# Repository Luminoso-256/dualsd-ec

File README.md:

# dualsd-ec
SD + MicroSD in one expansion card. It's a tight fit!

Based on the framework PCB template. Case is modified from the non-retrofit one, and doctored up to fit the slightly oversized PCB.

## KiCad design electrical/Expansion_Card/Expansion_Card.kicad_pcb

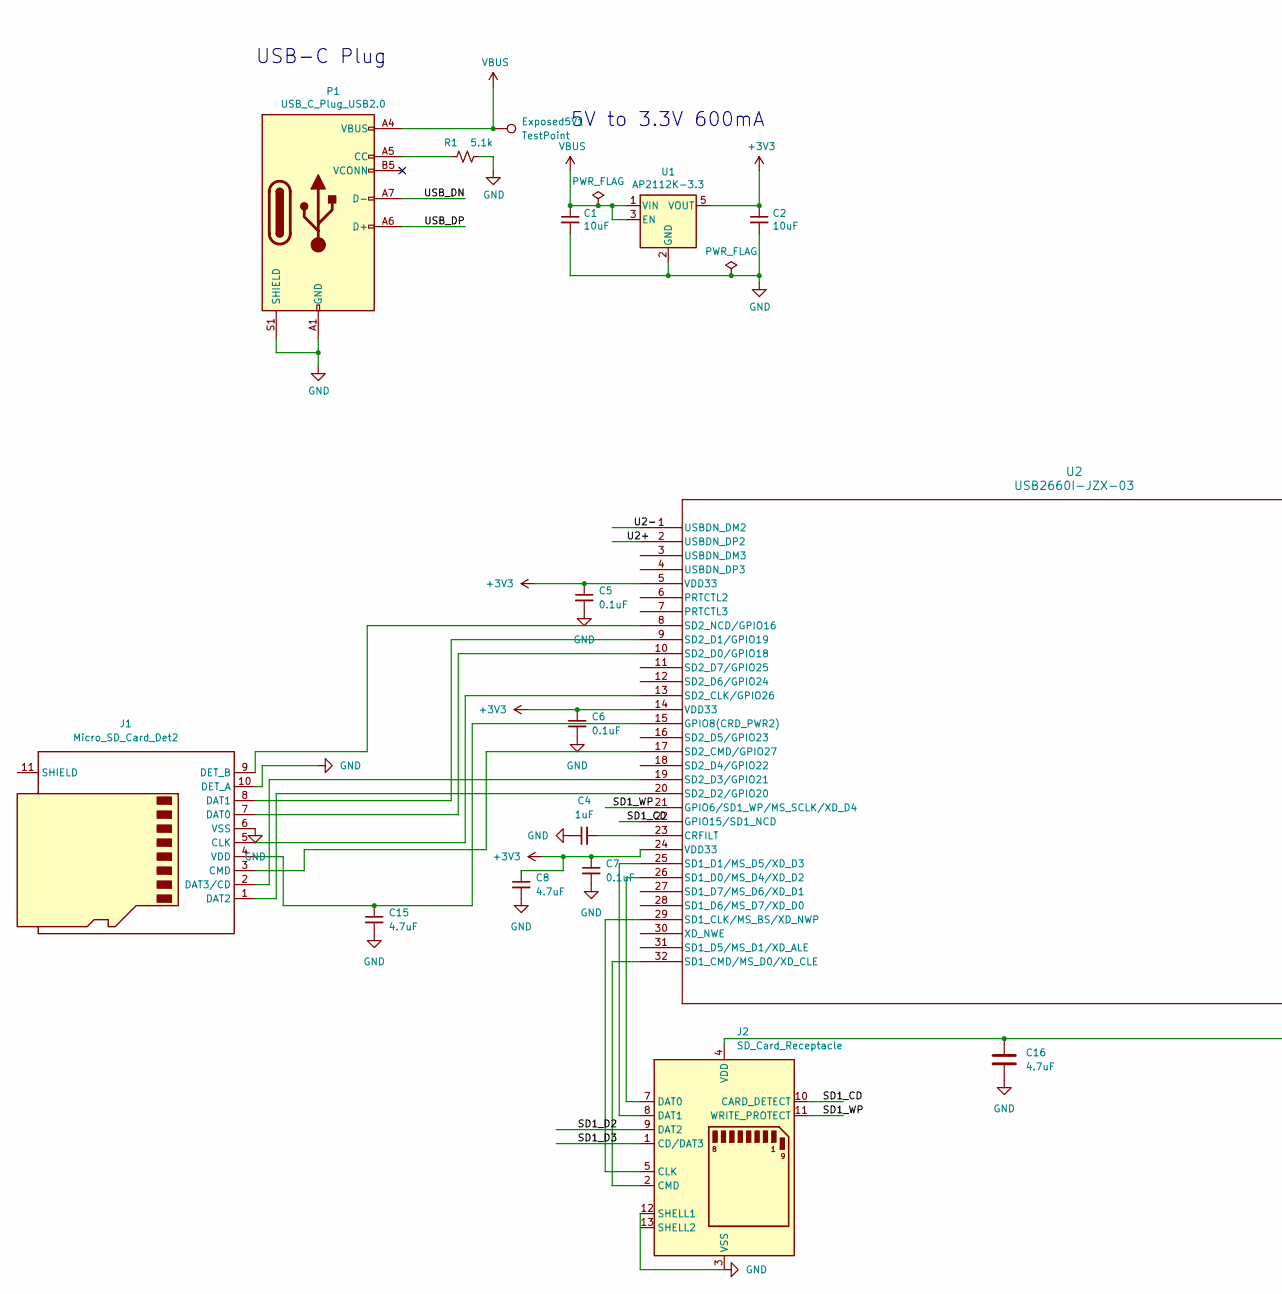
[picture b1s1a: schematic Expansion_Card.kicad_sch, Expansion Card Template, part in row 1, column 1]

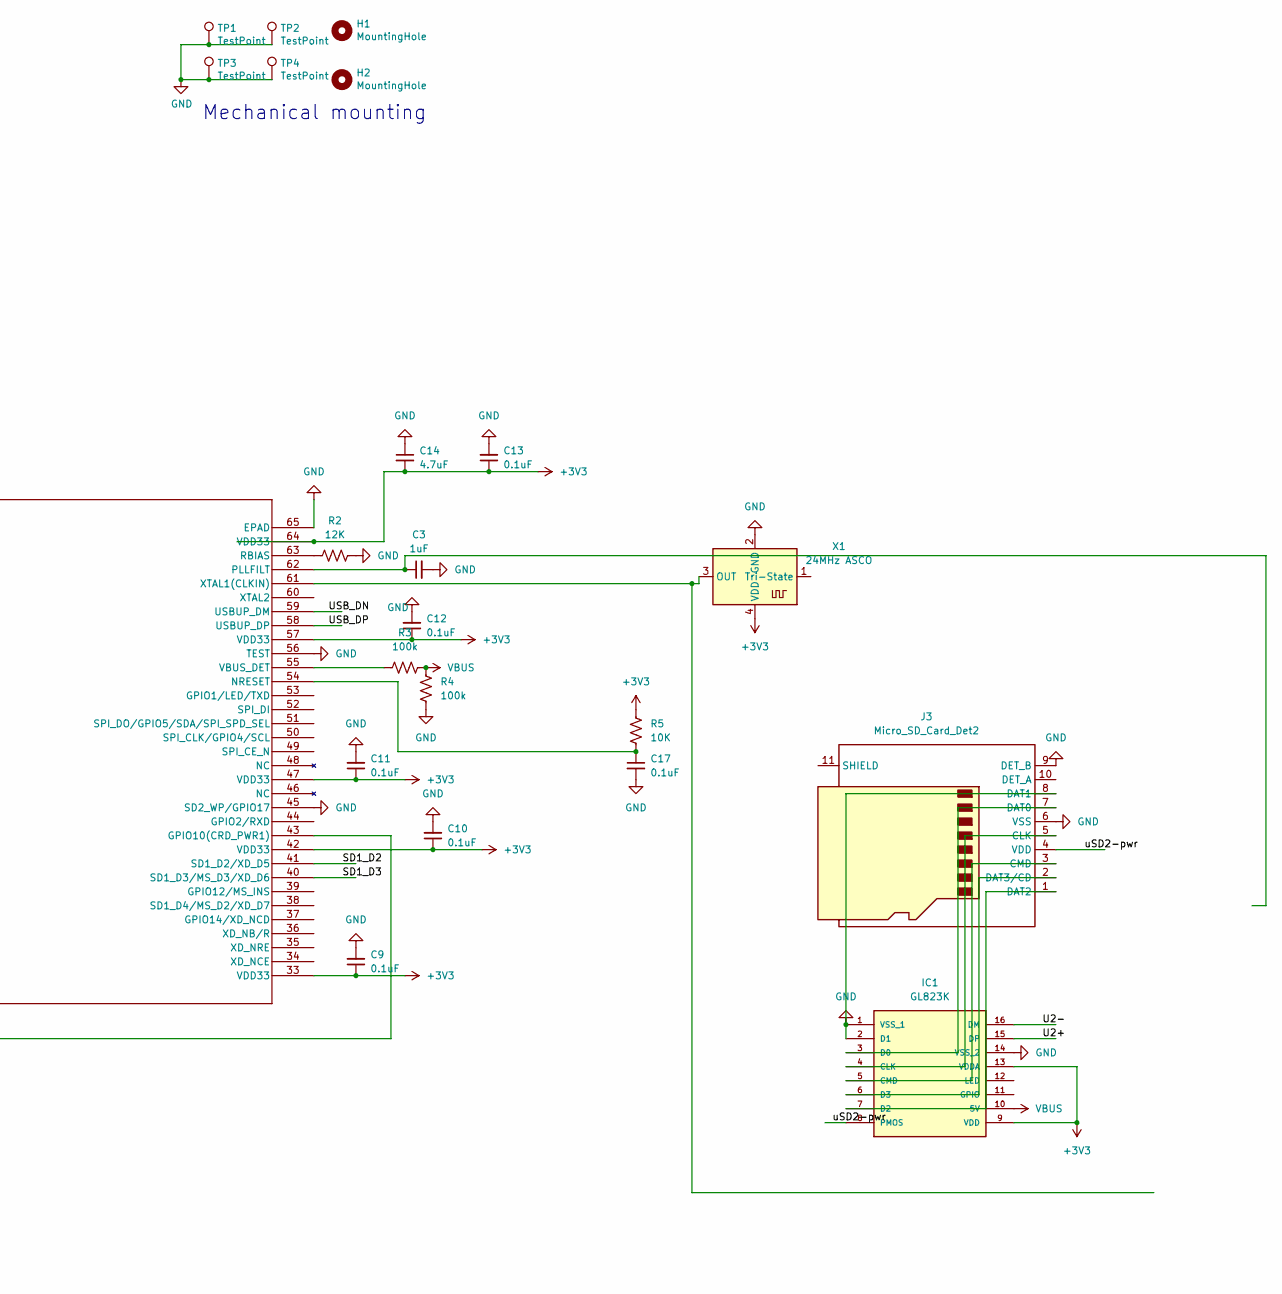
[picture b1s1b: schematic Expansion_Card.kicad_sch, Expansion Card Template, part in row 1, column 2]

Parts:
C1, C2: 10uF; C_0805_2012Metric
C3, C4: 1uF; C_0402_1005Metric
C5, C6, C7, C9, C10, C11, C12, C13, C17: 0.1uF; C_0402_1005Metric
C8, C14, C15, C16: 4.7uF; C_0402_1005Metric
Exposed5V1: TestPoint; TestPoint_Pad_2.0x2.0mm
H1, H2: MountingHole; MountingHole_2.2mm_M2
IC1: GL823K; SOP64P600X175-16N; MANUFACTURER_PART_NUMBER GL823K
J1, J3: Micro_SD_Card_Det2; microSD_HC_Molex_104031-0811
J2: SD_Card_Receptacle; CUI_SD-4-B
P1: USB_C_Plug_USB2.0; USB_C_Plug_Molex_105444
R1: 5.1k; R_0603_1608Metric
R2: 12K; R_0402_1005Metric
R3, R4: 100k; R_0402_1005Metric
R5: 10K; R_0402_1005Metric
TP1, TP2, TP3, TP4: TestPoint; TestPoint_Pad_1.5x1.5mm
U1: AP2112K-3.3; SOT-23-5
U2: USB2660I-JZX-03; QFN64_9x9MC_MCH
X1: 24MHz ASCO; Oscillator_SMD_Abracon_ASCO-4Pin_1.6x1.2mm

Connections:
+3V3: C2.1, C5.1, C6.1, C7.1, C8.1, C9.1, C10.1, C11.1, C12.1, C13.1, C14.2, IC1.9 (VDD), IC1.13 (VDDA), R5.1, U1.5 (VOUT), U2.5 (VDD33), U2.14 (VDD33), U2.24 (VDD33), U2.33 (VDD33), U2.42 (VDD33), U2.47 (VDD33), U2.57 (VDD33), U2.64 (VDD33), X1.4 (VDD)
/SD1_CD: J2.10 (CARD_DETECT), U2.22 (GPIO15/SD1_NCD)
/SD1_D2: J2.9 (DAT2), U2.41 (SD1_D2/XD_D5)
/SD1_D3: J2.1 (CD/DAT3), U2.40 (SD1_D3/MS_D3/XD_D6)
/SD1_WP: J2.11 (WRITE_PROTECT), U2.21 (GPIO6/SD1_WP/MS_SCLK/XD_D4)
/U2+: IC1.15 (DP), U2.2 (USBDN_DP2)
/U2-: IC1.16 (DM), U2.1 (USBDN_DM2)
/USB_DN: P1.A7 (D-), U2.59 (USBUP_DM)
/USB_DP: P1.A6 (D+), U2.58 (USBUP_DP)
/uSD2-pwr: IC1.8 (PMOS), J3.4 (VDD)
GND: C1.2, C2.2, C3.2, C4.1, C5.2, C6.2, C7.2, C8.2, C9.2, C10.2, C11.2, C12.2, C13.2, C14.1, C15.2, C16.2, C17.2, IC1.1 (VSS_1), IC1.2 (D1), IC1.14 (VSS_2), J1.6 (VSS), J1.10 (DET_A), J2.3 (VSS), J2.6 (VSS), J2.12 (SHELL1), J3.6 (VSS), J3.8 (DAT1), J3.9 (DET_B), P1.A1 (GND), P1.A12 (GND), P1.B1 (GND), P1.B12 (GND), P1.S1 (SHIELD), R1.2, R2.2, R4.1, TP1.1, TP2.1, TP3.1, TP4.1, U1.2 (GND), U2.45 (SD2_WP/GPIO17), U2.56 (TEST), U2.65 (EPAD), X1.2 (GND); also elsewhere on the board
unnamed: IC1.4 (CLK), J3.5 (CLK)
unnamed: IC1.5 (CMD), J3.3 (CMD)
unnamed: IC1.3 (D0), J3.7 (DAT0)
unnamed: IC1.7 (D2), J3.1 (DAT2)
unnamed: IC1.6 (D3), J3.2 (DAT3/CD)
unnamed: J1.5 (CLK), U2.13 (SD2_CLK/GPIO26)
unnamed: J1.3 (CMD), U2.17 (SD2_CMD/GPIO27)
unnamed: J1.7 (DAT0), U2.10 (SD2_D0/GPIO18)
unnamed: J1.8 (DAT1), U2.9 (SD2_D1/GPIO19)
unnamed: J1.1 (DAT2), U2.20 (SD2_D2/GPIO20)
unnamed: J1.2 (DAT3/CD), U2.19 (SD2_D3/GPIO21)
unnamed: J1.9 (DET_B), U2.8 (SD2_NCD/GPIO16)
unnamed: C15.1, J1.4 (VDD), U2.15 (GPIO8(CRD_PWR2))
unnamed: J2.5 (CLK), U2.29 (SD1_CLK/MS_BS/XD_NWP)
unnamed: J2.2 (CMD), U2.32 (SD1_CMD/MS_D0/XD_CLE)
unnamed: J2.7 (DAT0), U2.26 (SD1_D0/MS_D4/XD_D2)
unnamed: J2.8 (DAT1), U2.25 (SD1_D1/MS_D5/XD_D3)
unnamed: C16.1, J2.4 (VDD), U2.43 (GPIO10(CRD_PWR1))
unnamed: P1.A5 (CC), R1.1
unnamed: C4.2, U2.23 (CRFILT)
unnamed: C17.1, R5.2, U2.54 (NRESET)
unnamed: C3.1, U2.62 (PLLFILT)
unnamed: R2.1, U2.63 (RBIAS)
unnamed: R3.1, U2.55 (VBUS_DET)
unnamed: U2.61 (XTAL1(CLKIN)), X1.3 (OUT)
VBUS: C1.1, Exposed5V1.1, IC1.10 (5V), P1.A4 (VBUS), P1.A9 (VBUS), P1.B4 (VBUS), P1.B9 (VBUS), R3.2, R4.2, U1.1 (VIN), U1.3 (EN); also elsewhere on the board

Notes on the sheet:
Mechanical mounting
USB-C Plug
5V to 3.3V 600mA

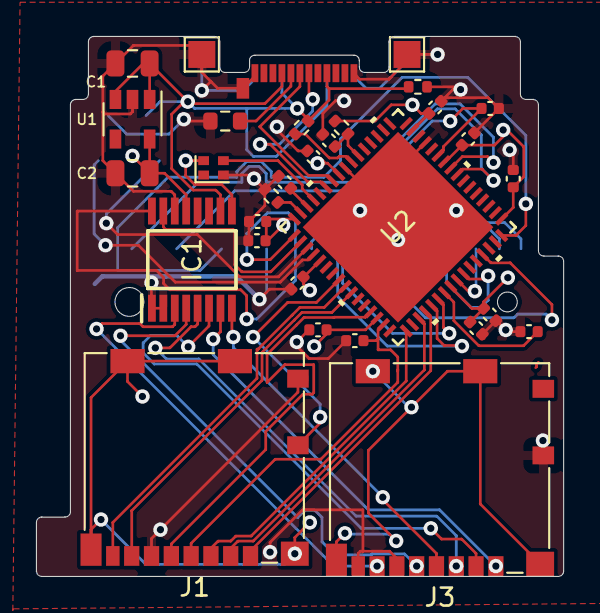
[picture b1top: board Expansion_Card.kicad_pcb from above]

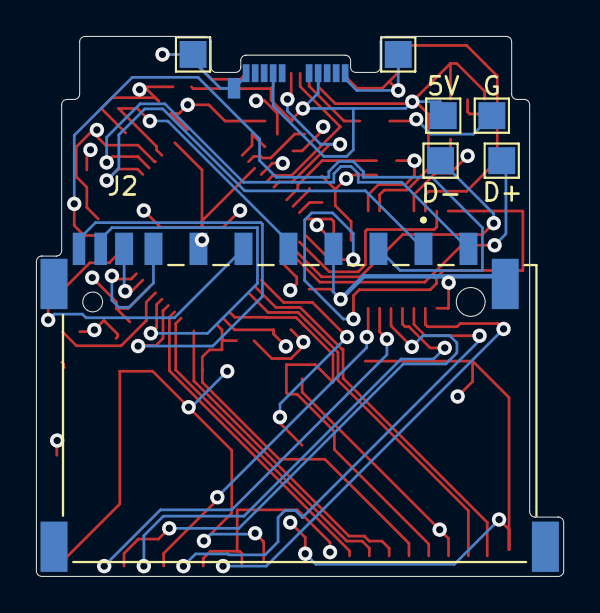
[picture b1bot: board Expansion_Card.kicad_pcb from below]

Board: 4 copper layers, 29.3 x 30.0 mm, 38 parts (7 on the bottom side), 37 nets.

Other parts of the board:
5V: TestPoint_Pad_1.5x1.5mm
D+: TestPoint_Pad_1.5x1.5mm
D-: TestPoint_Pad_1.5x1.5mm
G: TestPoint_Pad_1.5x1.5mm

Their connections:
GND: G.1; also elsewhere on the board
VBUS: 5V.1; also elsewhere on the board

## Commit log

2025-03-18 Snapshot Mechnical & Electrical into Git Repo
2025-03-18 finish routing USB pads for Rev2
2025-03-19 I have regrets
2025-03-19 restore pads to access 2nd downstream USB2.0 on the backside

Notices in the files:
electrical/Expansion_Card/Expansion_Card.kicad_pcb:
This work is licensed under a Creative Commons Attribution 4.0 International License
